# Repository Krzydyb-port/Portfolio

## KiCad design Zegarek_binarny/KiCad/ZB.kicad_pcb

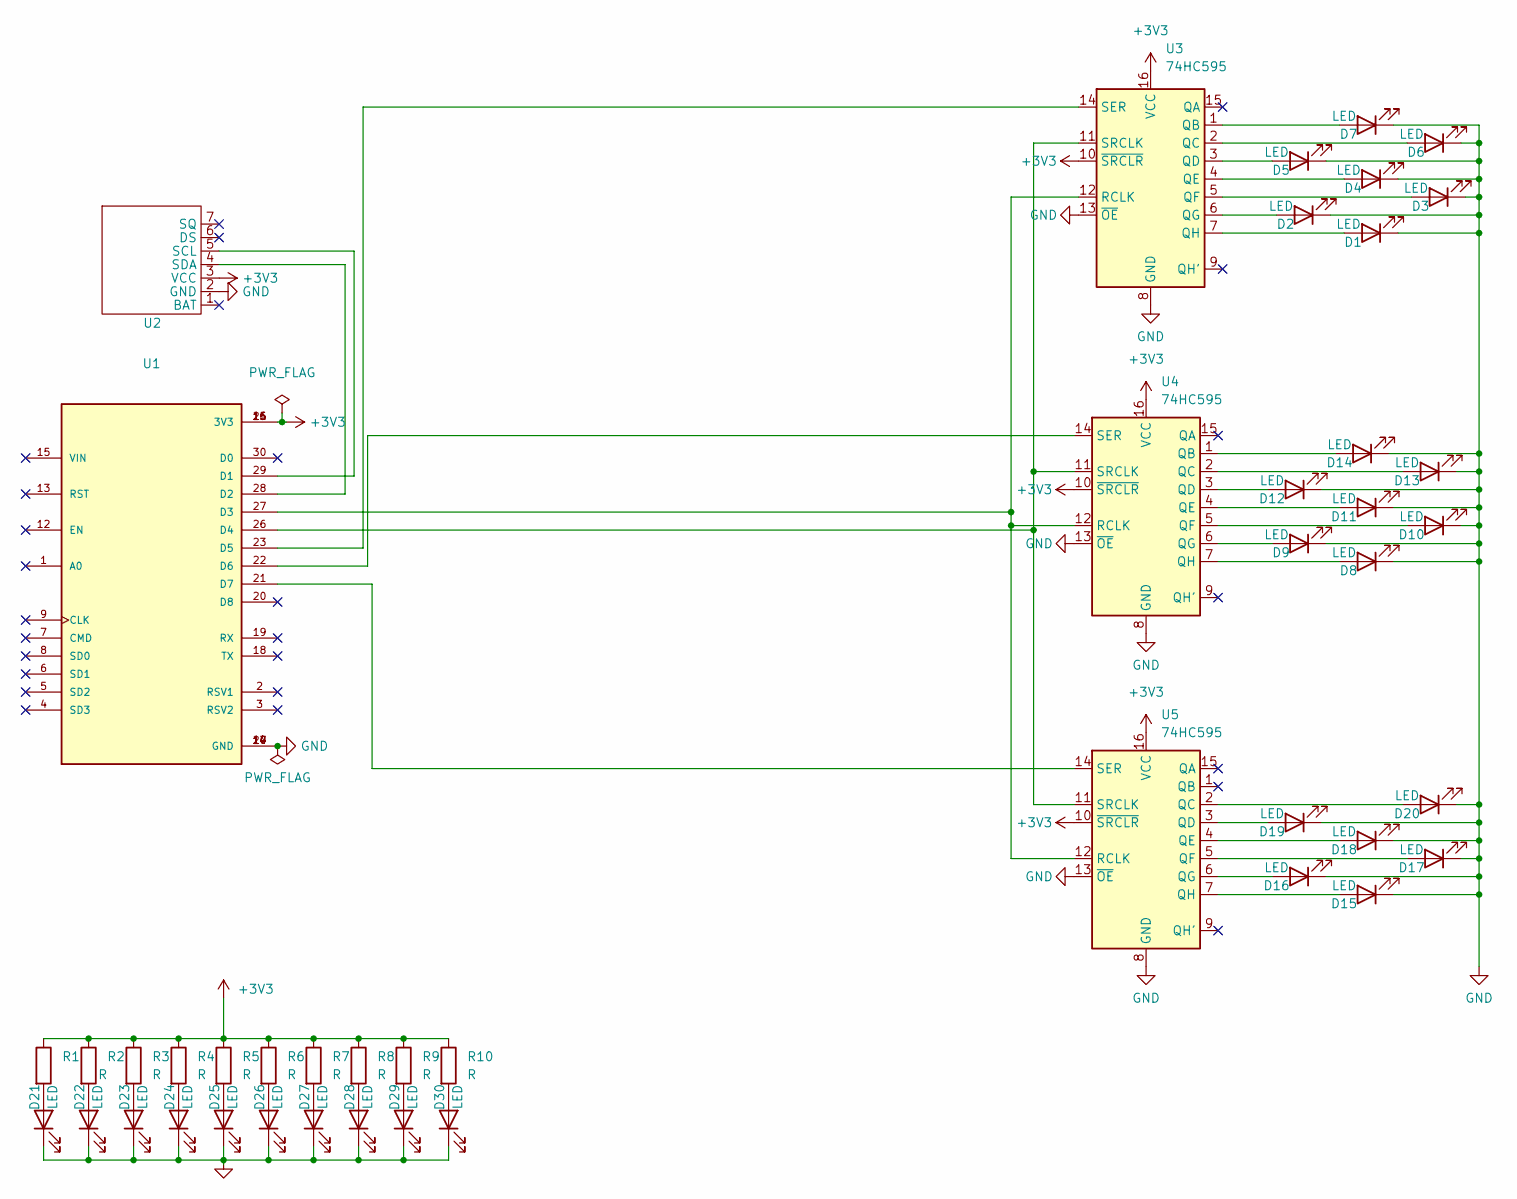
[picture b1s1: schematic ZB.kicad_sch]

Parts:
D1, D2, D3, D4, D5, D6, D7, D8, D9, D10, D11, D12, D13, D14, D15, D16, D17, D18, D19, D20, D21, D22, D23, D24, D25, D26, D27, D28, D29, D30: LED
R1: (no value)
R2, R3, R4, R5, R6, R7, R8, R9, R10: R
U1: PARTREV 1.0
U2: (no value)
U3, U4, U5: 74HC595; DIP-16_W7.62mm

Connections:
+3V3: R1.1, R2.1, R3.1, R4.1, R5.1, R6.1, R7.1, R8.1, R9.1, R10.1, U1.11 (3V3), U1.16 (3V3), U1.25 (3V3), U2.3 (VCC), U3.10 (~SRCLR), U3.16 (VCC), U4.10 (~SRCLR), U4.16 (VCC), U5.10 (~SRCLR), U5.16 (VCC)
unnamed: D1.2 (A), U3.7 (QH)
unnamed: D2.2 (A), U3.6 (QG)
unnamed: D3.2 (A), U3.5 (QF)
unnamed: D4.2 (A), U3.4 (QE)
unnamed: D5.2 (A), U3.3 (QD)
unnamed: D6.2 (A), U3.2 (QC)
unnamed: D7.2 (A), U3.1 (QB)
unnamed: D8.2 (A), U4.7 (QH)
unnamed: D9.2 (A), U4.6 (QG)
unnamed: D10.2 (A), U4.5 (QF)
unnamed: D11.2 (A), U4.4 (QE)
unnamed: D12.2 (A), U4.3 (QD)
unnamed: D13.2 (A), U4.2 (QC)
unnamed: D14.2 (A), U4.1 (QB)
unnamed: D15.2 (A), U5.7 (QH)
unnamed: D16.2 (A), U5.6 (QG)
unnamed: D17.2 (A), U5.5 (QF)
unnamed: D18.2 (A), U5.4 (QE)
unnamed: D19.2 (A), U5.3 (QD)
unnamed: D20.2 (A), U5.2 (QC)
unnamed: D21.2 (A), R1.2
unnamed: D22.2 (A), R2.2
unnamed: D23.2 (A), R3.2
unnamed: D24.2 (A), R4.2
unnamed: D25.2 (A), R5.2
unnamed: D26.2 (A), R6.2
unnamed: D27.2 (A), R7.2
unnamed: D28.2 (A), R8.2
unnamed: D29.2 (A), R9.2
unnamed: D30.2 (A), R10.2
unnamed: U1.21 (D7), U5.14 (SER)
unnamed: U1.22 (D6), U4.14 (SER)
unnamed: U1.23 (D5), U3.14 (SER)
unnamed: U1.26 (D4), U3.11 (SRCLK), U4.11 (SRCLK), U5.11 (SRCLK)
unnamed: U1.27 (D3), U3.12 (RCLK), U4.12 (RCLK), U5.12 (RCLK)
unnamed: U1.28 (D2), U2.4 (SDA)
unnamed: U1.29 (D1), U2.5 (SCL)

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
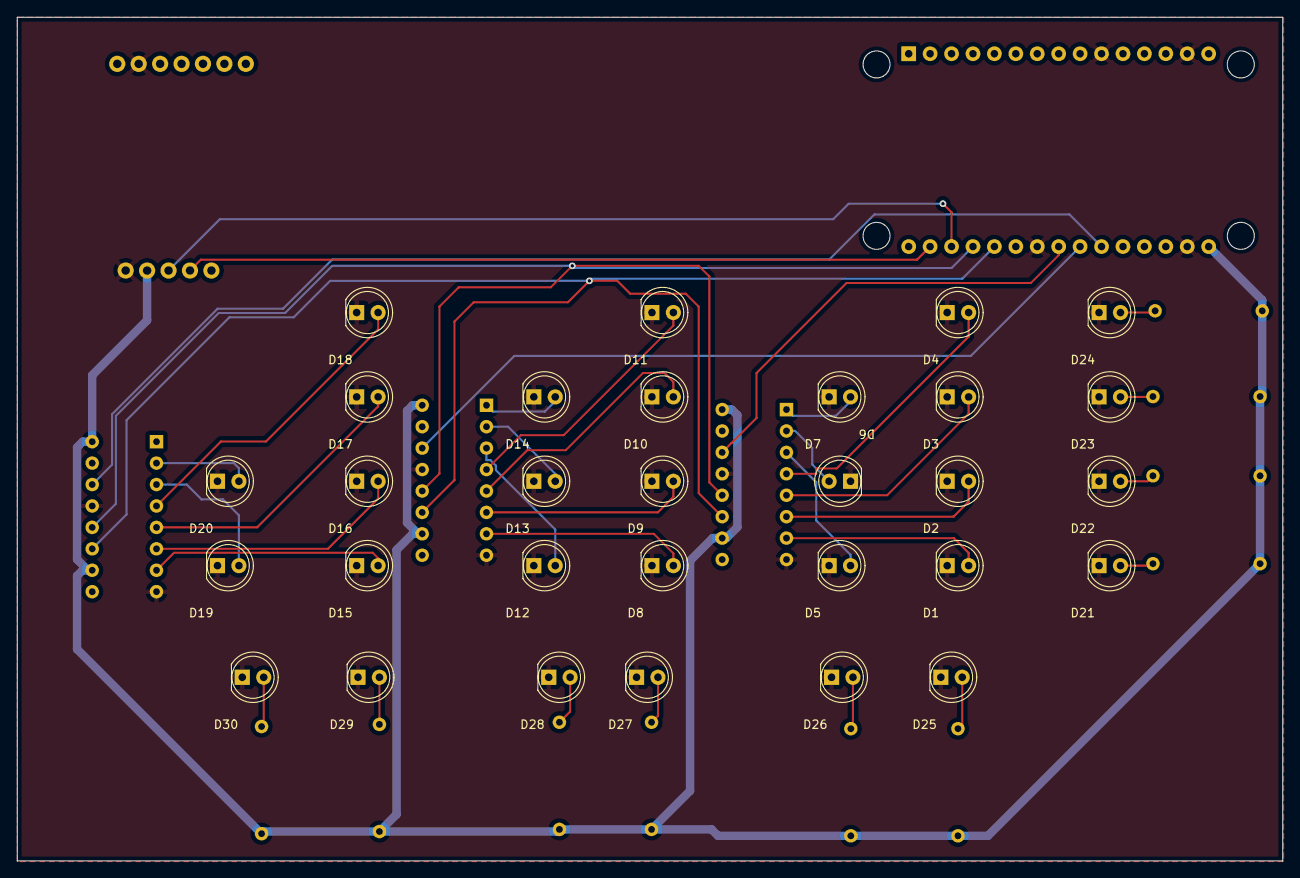
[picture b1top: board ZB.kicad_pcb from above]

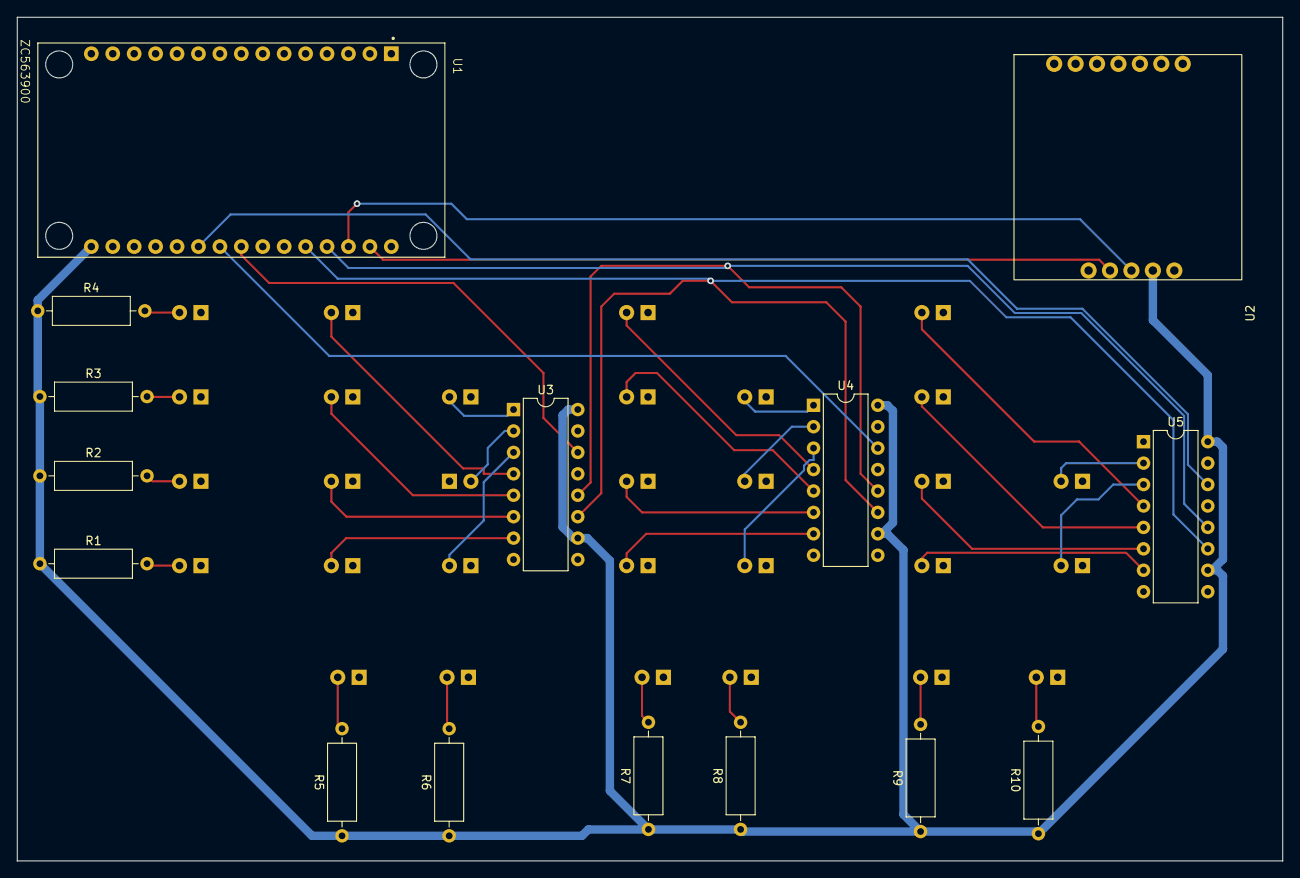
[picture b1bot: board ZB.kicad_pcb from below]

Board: 2 copper layers, 150.0 x 100.0 mm, 45 parts (15 on the bottom side), 39 nets.

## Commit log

2026-06-18 test
2026-06-18 Studia: projekt własnej implementacji gry bomberman
2026-06-18 Studia: Projekt aplikacji do zarządzania flotą pojazdów i kierowców
